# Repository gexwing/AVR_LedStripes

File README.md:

AVR_LedStripes
==============

Overview
-------
This Project uses an Atmega8 microcontroller to control RGB Led Stripes. The goal of this project is to have a nice modular platform with various modules to control the Color via IR Remote, Sound, or maybe other methods in the future.

src/ - The sourcecode for the Atmege, written in C.  
docs/ - documentation for hardware parts and application notes.  
eagle/ - CadSoft Eagle Schematics and Board Layout Files.  
TLSpice/ - Simulation files to test parts of the board schematics.  

Modules
-------
IRMP - Infrared Multiprotocol decoder  
SoftPWM - Software Pulse-Width-Modulation with 3 Channels via Timer Interrupt

TODO
-------
[x] Bring code upto date for v2 Board  
[] investigate gamma correction for PWM Module  
[] Add a microphone with preamp to the board for sound sampling.  
[] Add a FFT Module for anazyling sound spectrums.  
[] Add Mode for Sounds Controled Lighting  

Links
-------
Using Lookup Tables for Gamma Correction on LEDs: http://www.maximintegrated.com/app-notes/index.mvp/id/3667  
Fixed-Point FFT for Atmega: http://elm-chan.org/works/akilcd/report_e.html  
Infrared-Multiprotocol-Decoder: http://www.mikrocontroller.net/articles/IRMP  

License
-------
TBA

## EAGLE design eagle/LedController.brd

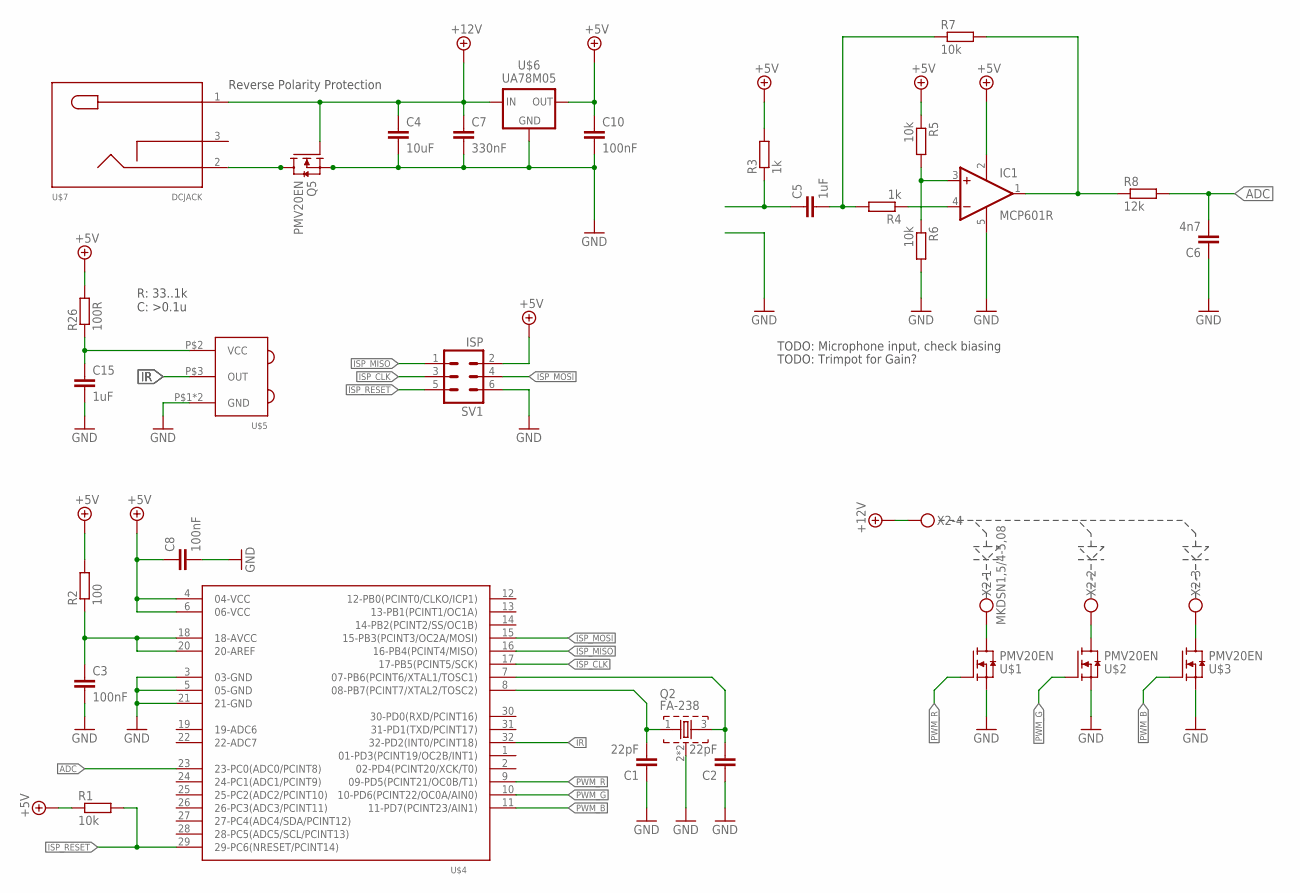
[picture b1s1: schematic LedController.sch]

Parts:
C1, C2: 22pF; C0805
C3, C8, C10: 100nF; C0805
C4: 10uF; C0805
C5, C15: 1uF; C0805
C6: 4n7; C0805
C7: 330nF; C0805
IC1: MCP601R; SOT23-5
Q2: FA-238
Q5: PMV20EN; SOT23
R1, R5, R6, R7: 10k; R0805
R2: 100; R0805
R3: 1k; M0805
R4: 1k; R0805
R8: 12k; R0805
R26: 100R; R0805
SV1: ISP; MA03-2
U$1, U$2, U$3: PMV20EN; SOT23
U$4: ATMEGA328; TQFP32
U$5: TSOP75236
U$6: UA78M05; SOT-223
U$7: DCJACK
X2: MKDSN1,5/4-5,08

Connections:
+5V: C8.1, C10.1, IC1.2 (V+), R1.1, R2.2, R3.2, R5.1, R26.2, SV1.2, U$4.4 (04-VCC), U$4.6 (06-VCC), U$6.3 (OUT)
+12V: C4.1, C7.1, Q5.1 (G), U$6.1 (IN), U$7.1, X2.4
ADC: C6.2, R8.2, U$4.23 (23-PC0(ADC0/PCINT8))
GND: C1.1, C2.1, C3.2, C4.2, C6.1, C7.2, C8.2, C10.2, C15.2, IC1.5 (V-), Q2.2, Q2.4 (2), Q5.2 (S), R6.2, SV1.6, U$1.2 (S), U$2.2 (S), U$3.2 (S), U$4.3 (03-GND), U$4.5 (05-GND), U$4.21 (21-GND), U$5.P$1 (GND), U$5.P$4 (GND), U$6.2 (GND), U$6.TER (GND)
IR: U$4.32 (32-PD2(INT0/PCINT18)), U$5.P$3 (OUT)
ISP_CLK: SV1.3, U$4.17 (17-PB5(PCINT5/SCK))
ISP_MISO: SV1.1, U$4.16 (16-PB4(PCINT4/MISO))
ISP_MOSI: SV1.4, U$4.15 (15-PB3(PCINT3/OC2A/MOSI))
ISP_RESET: R1.2, SV1.5, U$4.29 (29-PC6(NRESET/PCINT14))
unnamed: C5.1, R3.1
unnamed: U$1.3 (D), X2.1
unnamed: U$2.3 (D), X2.2
unnamed: U$3.3 (D), X2.3
unnamed: C3.1, R2.1, U$4.18 (18-AVCC), U$4.20 (20-AREF)
unnamed: Q5.3 (D), U$7.2
unnamed: C5.2, R4.2, R7.1
unnamed: IC1.4 (-IN), R4.1
unnamed: IC1.3 (+IN), R5.2, R6.1
unnamed: IC1.1 (OUT), R7.2, R8.1
unnamed: C1.2, Q2.1, U$4.8 (08-PB7(PCINT7/XTAL2/TOSC2))
unnamed: C2.2, Q2.3, U$4.7 (07-PB6(PCINT6/XTAL1/TOSC1))
unnamed: C15.1, R26.1, U$5.P$2 (VCC)
PWM_B: U$3.1 (G), U$4.11 (11-PD7(PCINT23/AIN1))
PWM_G: U$2.1 (G), U$4.10 (10-PD6(PCINT22/OC0A/AIN0))
PWM_R: U$1.1 (G), U$4.9 (09-PD5(PCINT21/OC0B/T1))

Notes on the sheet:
Reverse Polarity Protection
R: 33..1k C: >0.1u
TODO: Microphone input, check biasing
TODO: Trimpot for Gain?

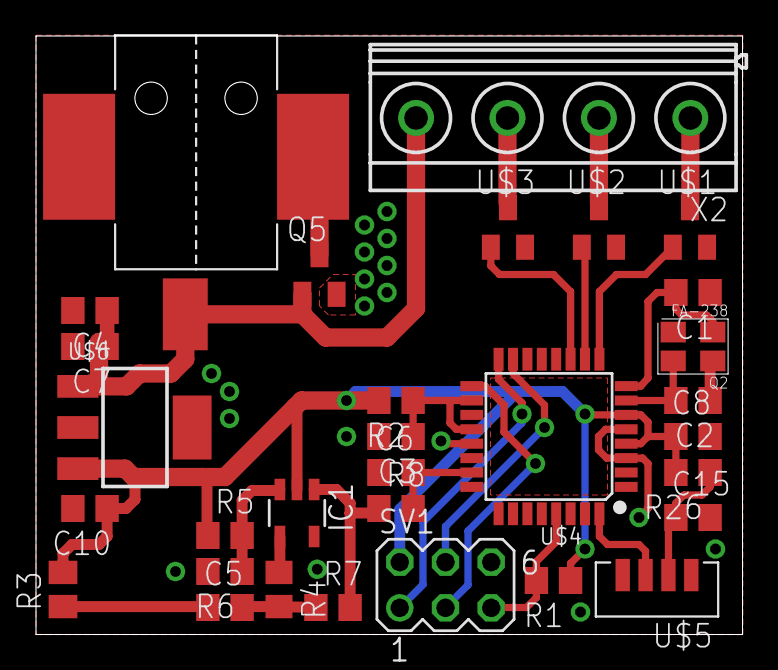
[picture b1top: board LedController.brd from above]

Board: 2 copper layers, 39.2 x 33.2 mm, 31 parts (0 on the bottom side), 25 nets.

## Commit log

2013-04-06 Initial commit of old Code
2013-04-06 Cleanup of metadata folders
2013-04-06 Cleanup of structs
2013-04-07 Cleanup of Project Files
2013-04-07 Adding Eagle files
2013-04-08 Comments and Stuff
2013-04-08 Cleanup for new Eagle version
2013-04-09 Add reverse polarity protection
2013-04-09 Add Datasheet Links and Simulation Files.
2013-04-09 Ignore Datasheet PDF's
2013-04-09 Changing Signal Names, split up into individual parts in schematic
2013-04-13 add direct link for atmega8 datasheet
2013-04-13 Add digital recording appnote
2013-04-13 add preamp stage for microphone
2013-04-13 add preamp simulation, not yet functional
2013-04-13 Adding some usefull articles
2013-04-13 Cleanup & updating readme
2013-04-13 correcting linebreaks in readme
2013-04-13 add FFT reference
2013-04-30 new preamp circuit
2013-04-30 more sim stuff
2016-04-11 Replace atmega8 (DIP) with atmega328 (TQFP), start of redesign
2016-04-11 Change IR Receiver module to SMD variant
2016-04-11 Change voltage regulator to DPAK variant
2016-04-12 Add DC Barrel Jack
2016-04-12 Cosmetic Changes in Board Schematic
2016-04-12 Change crystal to SMD type
2016-05-12 Change ISP Connector, layout most things
2016-05-17 More relayouting, Framed schematic
